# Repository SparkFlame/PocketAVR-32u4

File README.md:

# PocketAVR-32u4

In this Repository you will find test software for hardware based on the Atmel ATMega32u4 USB Microcontroller.

##Directory Contents

* __/Bootloaders__ This contains the [LUFA] (http://www.fourwalledcubicle.com/LUFA.php) (Lightweight USB Framework for AVRs)
* __/Examples__ Contains example Code for use on the 32u4 board
 *  __/Input__ Shows basic input.
 *  __/Output__ Shows basic output.
 *  __/Library__ Contains a Makefile and other basic libraries and Header Files
* __/Hardware__ Contains Hardware files created in [CadSoft Eagle] (http://www.cadsoftusa.com/download-eagle/) 

##LUFA Bootloader

                   _   _ _ ___ _
                  | | | | | __/ \
                  | |_| U | _| o | - The Lightweight USB
                  |___|___|_||_n_|    Framework for AVRs
                =========================================
                          Written by Dean Camera
                  dean [at] fourwalledcubicle [dot] com

                         http://www.lufa-lib.org
                =========================================

               LUFA is donation supported. To support LUFA,
             please donate at http://www.lufa-lib.org/donate

               Released under a modified MIT license - see
                  [LUFA/License.txt] (https://github.com/abcminiuser/lufa) at  for license details.

                For Commercial Licensing information, see
                     http://www.lufa-lib.org/license

This package contains the complete LUFA library, demos, user-submitted
projects and bootloaders for use with compatible microcontroller models.
LUFA is a simple to use, lightweight framework which sits atop the hardware
USB controller in specific AVR microcontroller models, and allows for the
quick and easy creation of complex USB devices and hosts.

To get started, you will need to install the "Doxygen" documentation
generation tool. If you use Linux, this can be installed via the "doxygen"
package in your chosen package management tool - under Ubuntu, this can be
achieved by running the following command in the terminal:

   sudo apt-get install doxygen

Other package managers and distributions will have similar methods to
install Doxygen. In Windows, you can download a prebuilt installer for
Doxygen from its website, www.doxygen.org.

Once installed, you can then use the Doxygen tool to generate the library
documentation from the command line or terminal of your operating system. To
do this, open your terminal or command line to the root directory of the
LUFA package, and type the following command:

   make doxygen

Which will recursively generate documentation for all elements in the
library - the core, plus all demos, projects and bootloaders. Generated
documentation will then be available by opening the file "index.html" of the
created Documentation/html/ subdirectories inside each project folder.

The documentation for the library itself (but not the documentation for the
individual demos, projects or bootloaders) is also available as a separate
package from the project webpage for convenience if Doxygen cannot be
installed.

##Notes

__4-10-16__ Added Hardware schematic, board, and BOM to repository.

__4-13-16__ Changed Hardware Schematic to an updated v1.1.

__4-14-16__ Added new board with silkscreen

__4-16-16__ Added new board

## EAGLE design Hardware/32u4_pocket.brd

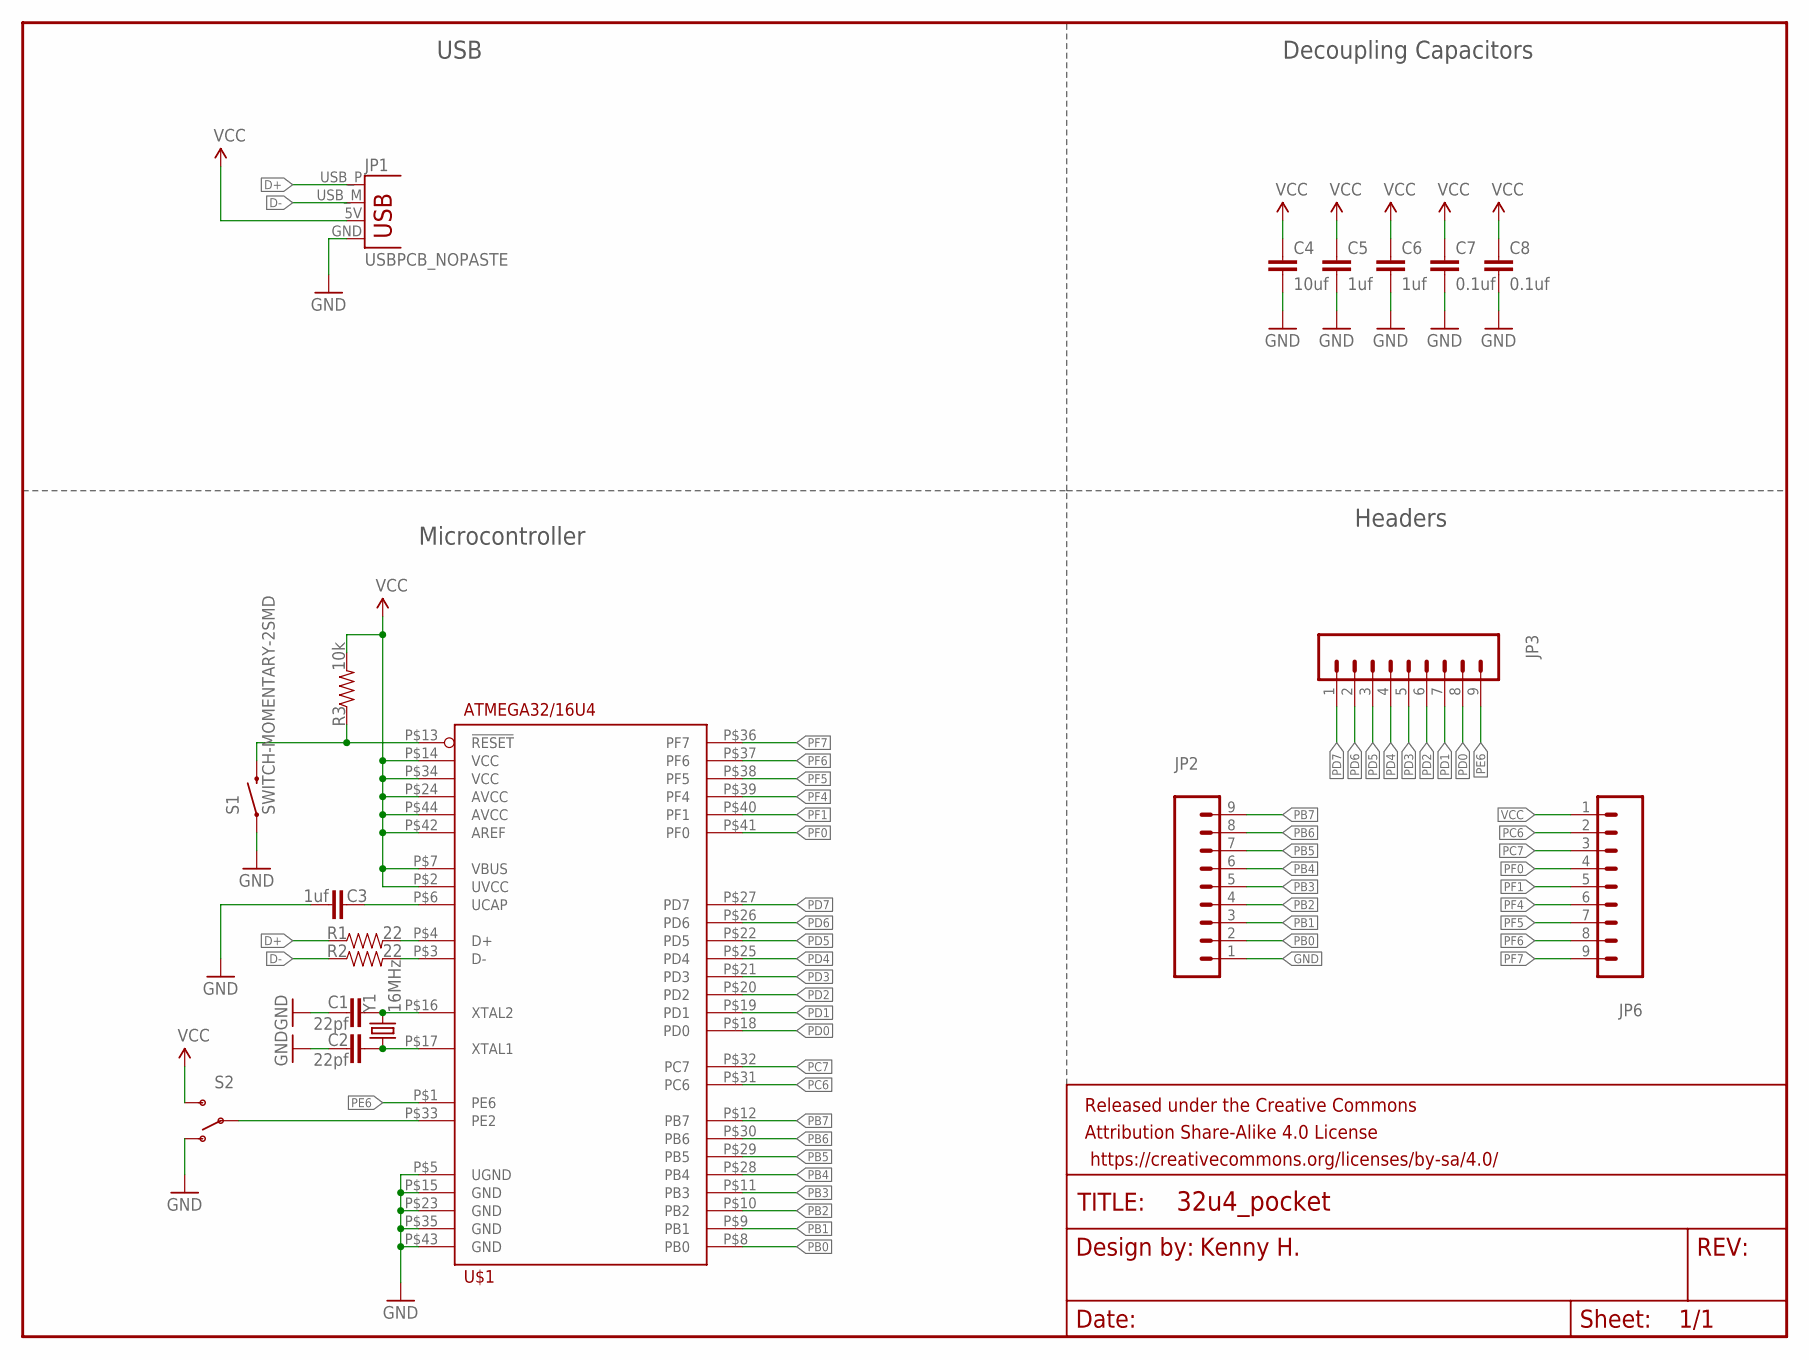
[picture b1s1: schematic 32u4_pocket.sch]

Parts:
C1, C2: 22pf; 0603-CAP
C3, C5, C6: 1uf; 0603-CAP
C4: 10uf; 0603-CAP
C7, C8: 0.1uf; 0603-CAP
FRAME1: FRAME-LETTER; CREATIVE_COMMONS
JP1: USBPCB_NOPASTE; USB-A-PCB-NOPASTE
JP2, JP3, JP6: M09LOCK-LONGPADS; 1X09_LOCK_LONGPADS
R1, R2: 22; 0603-RES
R3: 10k; 0603-RES
S1: SWITCH-MOMENTARY-2SMD; TACTILE-SWITCH-SMD
S2: SWITCH-SPDT-SMD-A; SWITCH-SPST-SMD-A
U$1: ATMEGA32/16U4; TQFP_44_0.8MM
Y1: 16MHz; HC49US

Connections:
D+: JP1.USB_P (D+), R1.1
D-: JP1.USB_M (D-), R2.1
GND: C1.1, C2.1, C3.2, C4.2, C5.2, C6.2, C7.2, C8.2, JP1.GND, JP2.1, S1.1, S2.1 (O), U$1.P$5 (UGND), U$1.P$15 (GND), U$1.P$23 (GND), U$1.P$35 (GND), U$1.P$43 (GND)
unnamed: R3.1, S1.3 (2), U$1.P$13 (!RESET)
unnamed: S2.2, U$1.P$33 (PE2)
unnamed: C2.2, U$1.P$17 (XTAL1), Y1.1
unnamed: C1.2, U$1.P$16 (XTAL2), Y1.2
unnamed: C3.1, U$1.P$6 (UCAP)
unnamed: R1.2, U$1.P$4 (D+)
unnamed: R2.2, U$1.P$3 (D-)
PB0: JP2.2, U$1.P$8 (PB0)
PB1: JP2.3, U$1.P$9 (PB1)
PB2: JP2.4, U$1.P$10 (PB2)
PB3: JP2.5, U$1.P$11 (PB3)
PB4: JP2.6, U$1.P$28 (PB4)
PB5: JP2.7, U$1.P$29 (PB5)
PB6: JP2.8, U$1.P$30 (PB6)
PB7: JP2.9, U$1.P$12 (PB7)
PC6: JP6.2, U$1.P$31 (PC6)
PC7: JP6.3, U$1.P$32 (PC7)
PD0: JP3.8, U$1.P$18 (PD0)
PD1: JP3.7, U$1.P$19 (PD1)
PD2: JP3.6, U$1.P$20 (PD2)
PD3: JP3.5, U$1.P$21 (PD3)
PD4: JP3.4, U$1.P$25 (PD4)
PD5: JP3.3, U$1.P$22 (PD5)
PD6: JP3.2, U$1.P$26 (PD6)
PD7: JP3.1, U$1.P$27 (PD7)
PE6: JP3.9, U$1.P$1 (PE6)
PF0: JP6.4, U$1.P$41 (PF0)
PF1: JP6.5, U$1.P$40 (PF1)
PF4: JP6.6, U$1.P$39 (PF4)
PF5: JP6.7, U$1.P$38 (PF5)
PF6: JP6.8, U$1.P$37 (PF6)
PF7: JP6.9, U$1.P$36 (PF7)
VCC: C4.1, C5.1, C6.1, C7.1, C8.1, JP1.5V (VBUS), JP6.1, R3.2, S2.3 (S), U$1.P$2 (UVCC), U$1.P$7 (VBUS), U$1.P$14 (VCC), U$1.P$24 (AVCC), U$1.P$34 (VCC), U$1.P$42 (AREF), U$1.P$44 (AVCC)

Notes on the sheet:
Microcontroller
USB
Decoupling Capacitors
Headers
Kenny H.

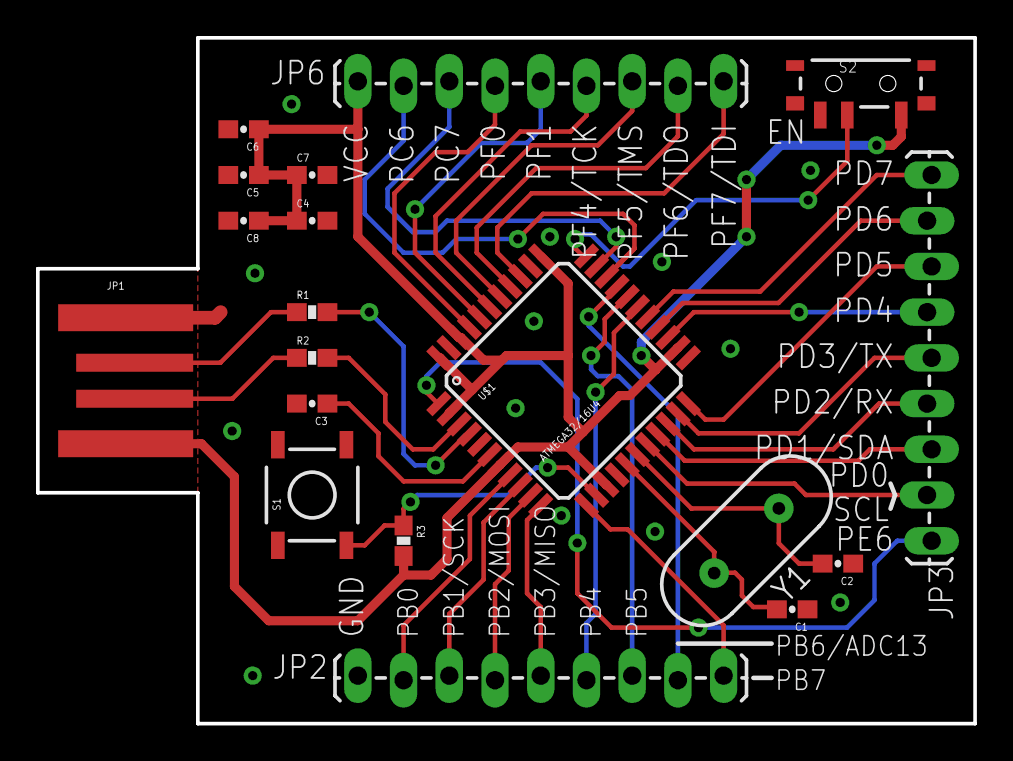
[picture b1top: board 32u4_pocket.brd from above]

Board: 2 copper layers, 52.1 x 38.1 mm, 20 parts (0 on the bottom side), 36 nets.

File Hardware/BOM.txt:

Qty Value                  Device                 Package            Parts         Description                                    
3                          M09LOCK-LONGPADS       1X09_LOCK_LONGPADS  JP2, JP3, JP6  Header 9                                     
2   0.1uf                  CAP0603-CAP            0603-CAP            C7, C8         Capacitor                                    
1   10k                    RESISTOR0603-RES       0603-RES            R3             Resistor                                     
1   10uf                   CAP0603-CAP            0603-CAP            C4             Capacitor                                    
1   16MHz                  CRYSTALHC49US          HC49US              Y1             Various standard crystals. Proven footprints.
3   1uf                    CAP0603-CAP            0603-CAP            C3, C5, C6     Capacitor                                    
2   22                     RESISTOR0603-RES       0603-RES            R1, R2         Resistor                                     
2   22pf                   CAP0603-CAP            0603-CAP            C1, C2         Capacitor                                    
1   ATMEGA32/16U4          ATMEGA32/16U4          TQFP_44_0.8MM       U$1            ATmega32u4 and 16u4                          
1   FRAME-LETTER           FRAME-LETTER           CREATIVE_COMMONS    FRAME1         Schematic Frame                              
1   SWITCH-MOMENTARY-2SMD  SWITCH-MOMENTARY-2SMD  TACTILE-SWITCH-SMD  S1             Various NO switches- pushbuttons, reed, etc  
1   USBPCB_NOPASTE         USBPCB_NOPASTE         USB-A-PCB-NOPASTE   JP1            USB Connectors

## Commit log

2016-04-04 Added files via upload
2016-04-04 Create Makefile
2016-04-04 Update Makefile
2016-04-04 Update LICENSE
2016-04-04 Rename LICENSE to LICENSE.md
    Changed name to work in Markdown and to change License
2016-04-05 Update Makefile
    Changed fuse defaults for ATMEGA32u4 from ATMEGA 328p
2016-04-06 Update README.md
    Added to Table of Contents to README for Navigation.
2016-04-06 Update Makefile
    Changed MCU to work when running MAKE
2016-04-06 Update makefile
    Changed values to match with 32u4 - still not complete. do not make .
2016-04-10 Update main.c
    Replaced bit-changing macros by showing code to work directly with the registers.
2016-04-13 Rename 32u4_pocket.txt to BOM.txt
2016-04-13 Delete hello.md
    Deleting dummy file
2016-04-14 Added files via upload
    New updated HW Files
2016-04-14 Rename 32u4_pocket.brd to Hardware/32u4_pocket.brd
2016-04-14 Rename 32u4_pocket.sch to Hardware/32u4_pocket.sch
2016-04-14 Rename BOM.txt to Hardware/BOM.txt
2016-04-15 Update README.md
    updated notes
2016-04-16 Update main.c
    Verified and changed bits set in register.
2016-04-16 Update main.c
    New update- do not know if it works.

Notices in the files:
parts and their libraries:
SparkFun-Capacitors: Licensing: Creative Commons ShareAlike 4.0 International - https://creativecommons.org/licenses/by-sa/4.0
SparkFun-Aesthetics: Released under the Creative Commons Attribution Share-Alike 4.0 License
SparkFun-Aesthetics: https://creativecommons.org/licenses/by-sa/4.0
